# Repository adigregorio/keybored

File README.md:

# keybored
let's just design a keyboard that we actually want to use I guess

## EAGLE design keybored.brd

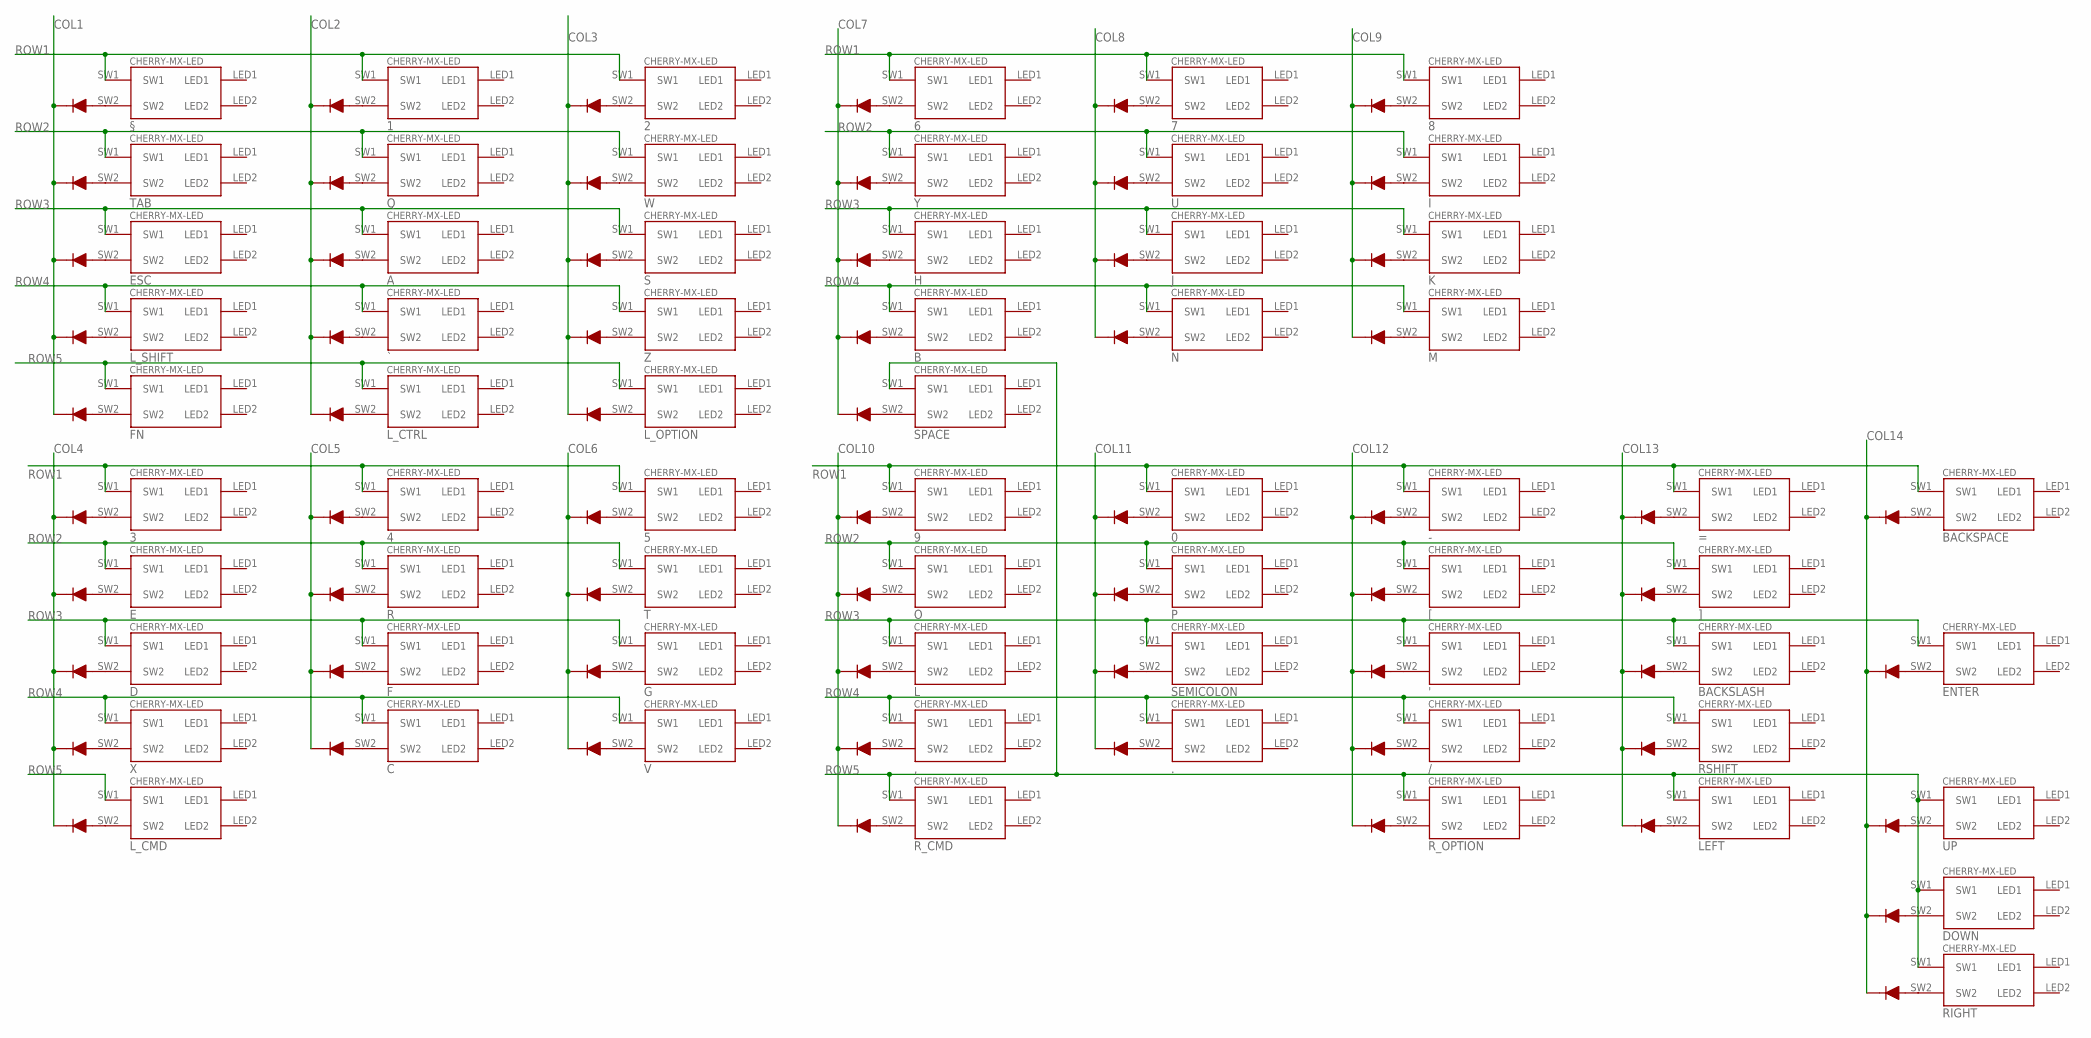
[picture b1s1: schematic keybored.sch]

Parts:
0, 1, 2, 3, 4, 5, 6, 7, 8, 9, .: CHERRY-MX-LED
': CHERRY-MX-LED
,: CHERRY-MX-LED
-: CHERRY-MX-LED
/: CHERRY-MX-LED
=: CHERRY-MX-LED
A: CHERRY-MX-LED
B: CHERRY-MX-LED
BACKSLASH: CHERRY-MX-LED
BACKSPACE: CHERRY-MX-LED
C: CHERRY-MX-LED
D: CHERRY-MX-LED
D1, D2, D3, D4, D5, D6, D7, D8, D9, D10, D11, D12, D13, D14, D15, D16, D17, D18, D19, D20, D21, D22, D23, D24, D25, D26, D27, D28, D29, D30, D31, D32, D33, D34, D35, D36, D37, D38, D39, D40, D41, D42, D43, D44, D45, D46, D47, D48, D49, D50, D51, D52, D53, D54, D55, D56, D57, D58, D59, D60, D61, D62, D63, D64, D65: DIODE_1N4148W; SOD123
DOWN: CHERRY-MX-LED
E: CHERRY-MX-LED
ENTER: CHERRY-MX-LED
ESC: CHERRY-MX-LED
F: CHERRY-MX-LED
FN: CHERRY-MX-LED
G: CHERRY-MX-LED
H: CHERRY-MX-LED
I: CHERRY-MX-LED
J: CHERRY-MX-LED
K: CHERRY-MX-LED
L: CHERRY-MX-LED
LEFT: CHERRY-MX-LED
L_CMD: CHERRY-MX-LED
L_CTRL: CHERRY-MX-LED
L_OPTION: CHERRY-MX-LED
L_SHIFT: CHERRY-MX-LED
M: CHERRY-MX-LED
N: CHERRY-MX-LED
O: CHERRY-MX-LED
P: CHERRY-MX-LED
Q: CHERRY-MX-LED
R: CHERRY-MX-LED
RIGHT: CHERRY-MX-LED
RSHIFT: CHERRY-MX-LED
R_CMD: CHERRY-MX-LED
R_OPTION: CHERRY-MX-LED
S: CHERRY-MX-LED
SEMICOLON: CHERRY-MX-LED
SPACE: CHERRY-MX-LED
T: CHERRY-MX-LED
TAB: CHERRY-MX-LED
U: CHERRY-MX-LED
UP: CHERRY-MX-LED
V: CHERRY-MX-LED
W: CHERRY-MX-LED
X: CHERRY-MX-LED
Y: CHERRY-MX-LED
Z: CHERRY-MX-LED
[: CHERRY-MX-LED
]: CHERRY-MX-LED
`: CHERRY-MX-LED
§: CHERRY-MX-LED

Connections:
COL1: D1.P$2, D7.P$2, D8.P$2, D9.P$2, D10.P$2
COL2: D2.P$2, D3.P$2, D4.P$2, D5.P$2, D6.P$2
COL3: D11.P$2, D12.P$2, D13.P$2, D14.P$2, D15.P$2
COL4: D26.P$2, D27.P$2, D28.P$2, D29.P$2, D30.P$2
COL5: D21.P$2, D22.P$2, D23.P$2, D24.P$2
COL6: D16.P$2, D17.P$2, D18.P$2, D19.P$2
COL7: D25.P$2, D31.P$2, D32.P$2, D33.P$2, D34.P$2
COL8: D37.P$2, D38.P$2, D39.P$2, D40.P$2
COL9: D42.P$2, D43.P$2, D44.P$2, D45.P$2
COL10: D20.P$2, D46.P$2, D47.P$2, D48.P$2, D49.P$2
COL11: D52.P$2, D53.P$2, D54.P$2, D55.P$2
COL12: D35.P$2, D56.P$2, D57.P$2, D58.P$2, D59.P$2
COL13: D36.P$2, D60.P$2, D61.P$2, D62.P$2, D63.P$2
COL14: D41.P$2, D50.P$2, D51.P$2, D64.P$2, D65.P$2
unnamed: D1.P$1, §.SW2
unnamed: 1.SW2, D2.P$1
unnamed: D3.P$1, Q.SW2
unnamed: A.SW2, D4.P$1
unnamed: D5.P$1, `.SW2
unnamed: D6.P$1, L_CTRL.SW2
unnamed: D7.P$1, TAB.SW2
unnamed: D8.P$1, ESC.SW2
unnamed: D9.P$1, L_SHIFT.SW2
unnamed: D10.P$1, FN.SW2
unnamed: 2.SW2, D11.P$1
unnamed: D12.P$1, W.SW2
unnamed: D13.P$1, S.SW2
unnamed: D14.P$1, Z.SW2
unnamed: D15.P$1, L_OPTION.SW2
unnamed: 5.SW2, D16.P$1
unnamed: D17.P$1, T.SW2
unnamed: D18.P$1, G.SW2
unnamed: D19.P$1, V.SW2
unnamed: D20.P$1, R_CMD.SW2
unnamed: 4.SW2, D21.P$1
unnamed: D22.P$1, R.SW2
unnamed: D23.P$1, F.SW2
unnamed: C.SW2, D24.P$1
unnamed: D25.P$1, SPACE.SW2
unnamed: 3.SW2, D26.P$1
unnamed: D27.P$1, E.SW2
unnamed: D.SW2, D28.P$1
unnamed: D29.P$1, X.SW2
unnamed: D30.P$1, L_CMD.SW2
unnamed: 6.SW2, D31.P$1
unnamed: D32.P$1, Y.SW2
unnamed: D33.P$1, H.SW2
unnamed: B.SW2, D34.P$1
unnamed: D35.P$1, R_OPTION.SW2
unnamed: D36.P$1, LEFT.SW2
unnamed: D37.P$1, N.SW2
unnamed: D38.P$1, J.SW2
unnamed: D39.P$1, U.SW2
unnamed: 7.SW2, D40.P$1
unnamed: D41.P$1, UP.SW2
unnamed: D42.P$1, M.SW2
unnamed: D43.P$1, K.SW2
unnamed: D44.P$1, I.SW2
unnamed: 8.SW2, D45.P$1
unnamed: 9.SW2, D46.P$1
unnamed: D47.P$1, O.SW2
unnamed: D48.P$1, L.SW2
unnamed: ,.SW2, D49.P$1
unnamed: D51.P$1, RIGHT.SW2
unnamed: ..SW2, D52.P$1
unnamed: D53.P$1, SEMICOLON.SW2
unnamed: D54.P$1, P.SW2
unnamed: 0.SW2, D55.P$1
unnamed: -.SW2, D56.P$1
unnamed: D57.P$1, [.SW2
unnamed: '.SW2, D58.P$1
unnamed: /.SW2, D59.P$1
unnamed: D50.P$1, DOWN.SW2
unnamed: D60.P$1, RSHIFT.SW2
unnamed: BACKSLASH.SW2, D61.P$1
unnamed: D62.P$1, ].SW2
unnamed: =.SW2, D63.P$1
unnamed: BACKSPACE.SW2, D64.P$1
unnamed: D65.P$1, ENTER.SW2
ROW1: 0.SW1, 1.SW1, 2.SW1, 3.SW1, 4.SW1, 5.SW1, 6.SW1, 7.SW1, 8.SW1, 9.SW1, -.SW1, =.SW1, BACKSPACE.SW1, §.SW1
ROW2: E.SW1, I.SW1, O.SW1, P.SW1, Q.SW1, R.SW1, T.SW1, TAB.SW1, U.SW1, W.SW1, Y.SW1, [.SW1, ].SW1
ROW3: '.SW1, A.SW1, BACKSLASH.SW1, D.SW1, ENTER.SW1, ESC.SW1, F.SW1, G.SW1, H.SW1, J.SW1, K.SW1, L.SW1, S.SW1, SEMICOLON.SW1
ROW4: ,.SW1, ..SW1, /.SW1, B.SW1, C.SW1, L_SHIFT.SW1, M.SW1, N.SW1, RSHIFT.SW1, V.SW1, X.SW1, Z.SW1, `.SW1
ROW5: DOWN.SW1, FN.SW1, LEFT.SW1, L_CMD.SW1, L_CTRL.SW1, L_OPTION.SW1, RIGHT.SW1, R_CMD.SW1, R_OPTION.SW1, SPACE.SW1, UP.SW1

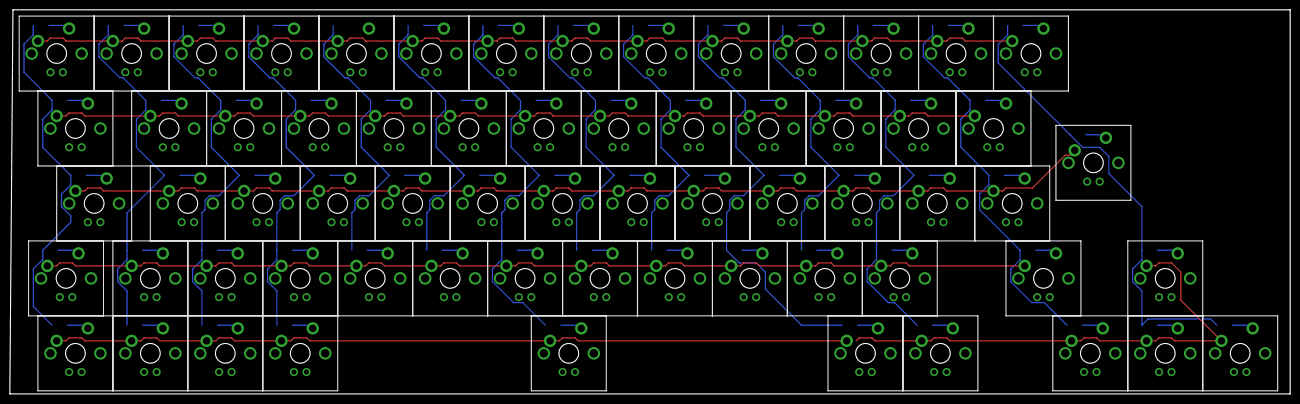
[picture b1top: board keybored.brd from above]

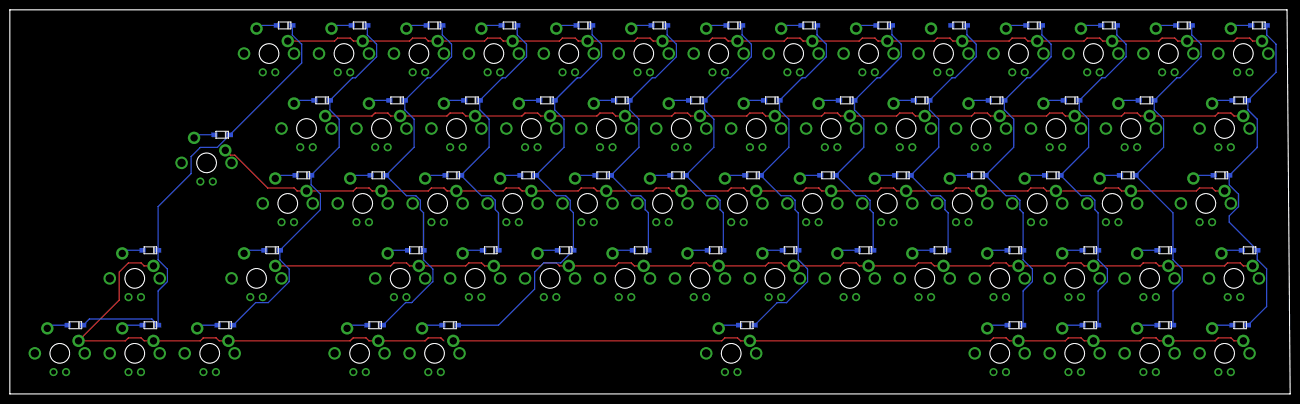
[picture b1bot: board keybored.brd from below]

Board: 2 copper layers, 260.4 x 78.1 mm, 130 parts (65 on the bottom side), 84 nets.

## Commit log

2018-03-14 schematic done i guess
2018-03-14 remove stupid eagle files
2018-03-14 fix gitignore
2018-03-15 preliminary layout
